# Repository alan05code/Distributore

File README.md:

# Distributore
Distributore Smart | Progetto Scolastico 2023/2024 | Client (PCB) + Server(RaspBerry) + SitoWeb(HTML/CSS/JavaScript) + Simulazione(Python)

Progetto esposto agli Open Day. Documentazione non terminata.

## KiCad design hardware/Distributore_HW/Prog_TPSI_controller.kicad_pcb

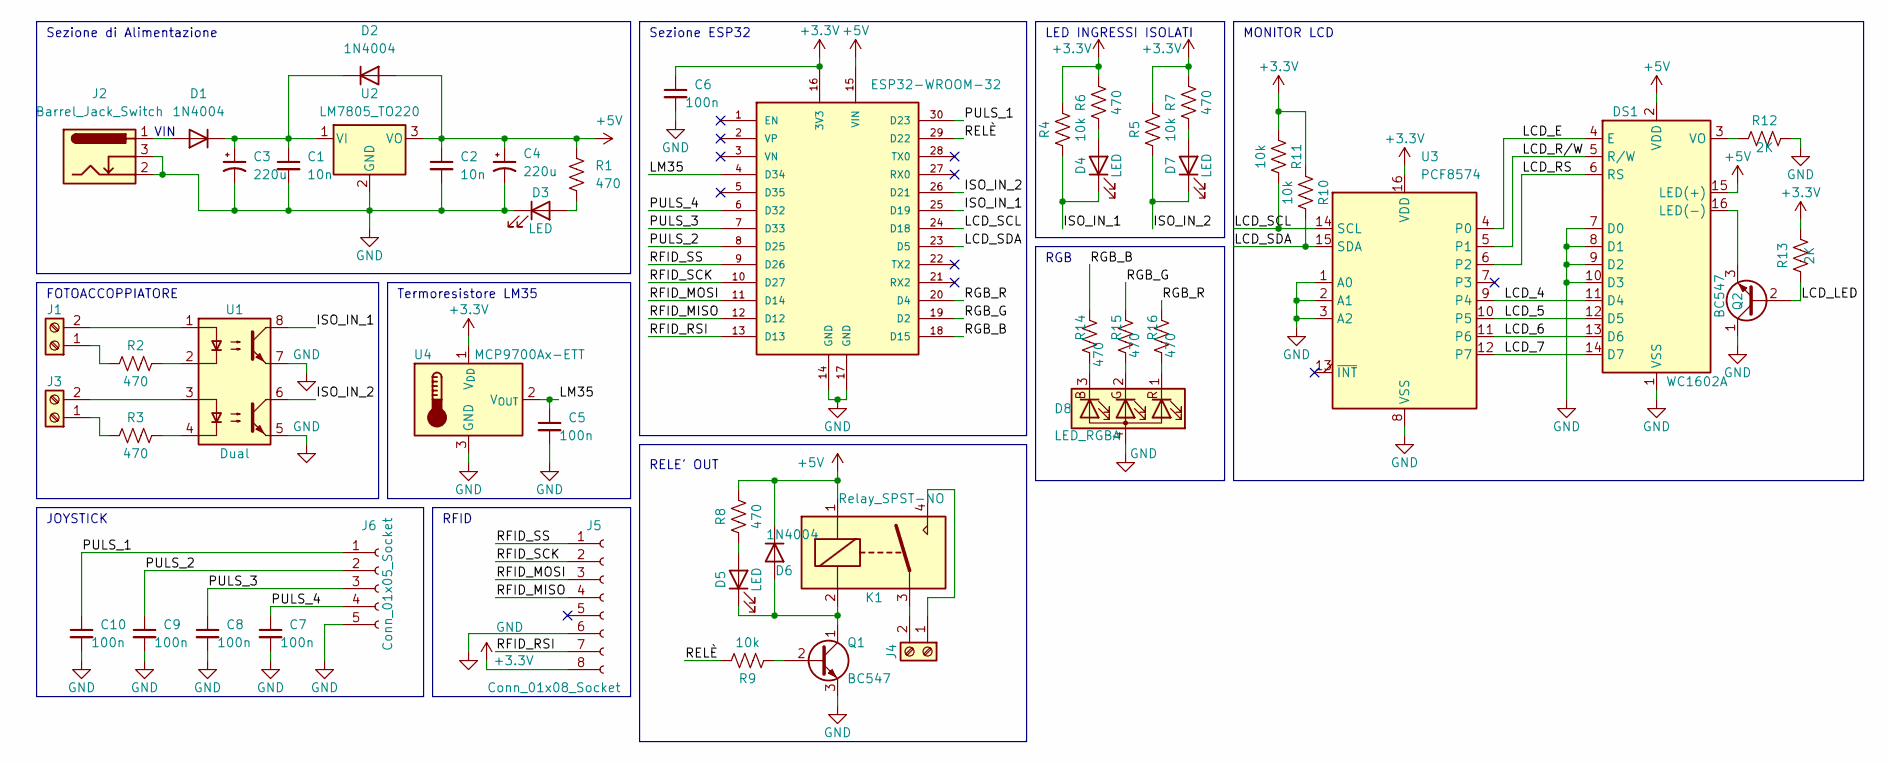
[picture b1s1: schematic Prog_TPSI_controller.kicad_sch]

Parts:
C1, C2: 10n; C_Disc_D7.0mm_W2.5mm_P5.00mm
C3, C4: 220u; CP_Radial_D5.0mm_P2.50mm
C5, C6, C7, C8, C9, C10: 100n; C_Disc_D7.0mm_W2.5mm_P5.00mm
D1, D2: 1N4004; D_DO-41_SOD81_P10.16mm_Horizontal
D3, D4, D5, D7: LED; LED_D5.0mm
D6: 1N4004; D_DO-41_SOD81_P7.62mm_Horizontal
D8: LED_RGBA; LED_D5.0mm-4_RGB_Wide_Pins
DS1: WC1602A; LCD
J1, J3, J4: Screw_Terminal_01x02; TerminalBlock_bornier-2_P5.08mm
J2: Barrel_Jack_Switch; Connettore_Alimentazione_Femmina_2.5mm
J5: Conn_01x08_Socket; PinSocket_1x08_P2.54mm_Horizontal
J6: Conn_01x05_Socket; PinSocket_1x05_P2.54mm_Horizontal
K1: Relay_SPST-NO; Rele_HF33F_CodiceRS_176-2640
Q1, Q2: BC547; TO-92L_Inline_Wide
R1, R8: 470; R_Axial_DIN0207_L6.3mm_D2.5mm_P7.62mm_Horizontal
R2, R3, R6, R7, R14, R15, R16: 470; R_Axial_DIN0207_L6.3mm_D2.5mm_P10.16mm_Horizontal
R4, R5, R10, R11: 10k; R_Axial_DIN0207_L6.3mm_D2.5mm_P10.16mm_Horizontal
R9: 10k; R_Axial_DIN0207_L6.3mm_D2.5mm_P15.24mm_Horizontal
R12: 2K; R_Axial_DIN0207_L6.3mm_D2.5mm_P10.16mm_Horizontal
R13: 2K; R_Axial_DIN0207_L6.3mm_D2.5mm_P7.62mm_Horizontal
S1: ESP32-WROOM-32; MODULE_ESP32_DEVKIT_V1; PARTREV N/A
U1: Dual; Socket_DIP-8_dual_DIP-4
U2: LM7805_TO220; TO-220-3_Horizontal_TabUp
U3: PCF8574; DIP-16_W7.62mm_Socket
U4: MCP9700Ax-ETT; TO-92_Inline_Wide

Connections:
+3.3V: C6.1, J5.8, R4.2, R5.2, R6.2, R7.2, R10.1, R11.1, R13.2, S1.16 (3V3), U3.16 (VDD), U4.1 (V_{DD})
+5V: C2.1, C4.1, D2.2 (A), D6.1 (K), DS1.2 (VDD), DS1.15 (LED(+)), K1.1, R1.1, R8.2, S1.15 (VIN), U2.3 (VO)
/ISO_IN_1: D4.1 (K), R4.1, S1.25 (D19), U1.8
/ISO_IN_2: D7.1 (K), R5.1, S1.26 (D21), U1.6
/LCD_4: DS1.11 (D4), U3.9 (P4)
/LCD_5: DS1.12 (D5), U3.10 (P5)
/LCD_6: DS1.13 (D6), U3.11 (P6)
/LCD_7: DS1.14 (D7), U3.12 (P7)
/LCD_E: DS1.4 (E), U3.4 (P0)
/LCD_LED: Q2.2 (B), R13.1
/LCD_RS: DS1.6 (RS), U3.6 (P2)
/LCD_R/W: DS1.5 (R/W), U3.5 (P1)
/LCD_SCL: R11.2, S1.24 (D18), U3.14 (SCL)
/LCD_SDA: R10.2, S1.23 (D5), U3.15 (SDA)
/LM35: C5.1, S1.4 (D34), U4.2 (V_{OUT})
/PULS_1: C10.1, J6.1, S1.30 (D23)
/PULS_2: C9.1, J6.2, S1.8 (D25)
/PULS_3: C8.1, J6.3, S1.7 (D33)
/PULS_4: C7.1, J6.4, S1.6 (D32)
/RELÈ: R9.2, S1.29 (D22)
/RFID_MISO: J5.4, S1.12 (D12)
/RFID_MOSI: J5.3, S1.11 (D14)
/RFID_RSI: J5.7, S1.13 (D13)
/RFID_SCK: J5.2, S1.10 (D27)
/RFID_SS: J5.1, S1.9 (D26)
/RGB_B: R14.2, S1.18 (D15)
/RGB_G: R15.2, S1.19 (D2)
/RGB_R: R16.2, S1.20 (D4)
GND: C1.2, C2.2, C3.2, C4.2, C5.2, C6.2, C7.2, C8.2, C9.2, C10.2, D3.1 (K), D8.4 (A), DS1.1 (VSS), DS1.7 (D0), DS1.8 (D1), DS1.9 (D2), DS1.10 (D3), J2.2, J2.3, J5.6, J6.5, Q1.3 (E), Q2.1 (C), R12.2, S1.14 (GND), S1.17 (GND), U1.5, U1.7, U2.2 (GND), U3.1 (A0), U3.2 (A1), U3.3 (A2), U3.8 (VSS), U4.3 (GND)
unnamed: D1.2 (A), J2.1
unnamed: C1.1, C3.1, D1.1 (K), D2.1 (K), U2.1 (VI)
unnamed: D3.2 (A), R1.2
unnamed: D4.2 (A), R6.1
unnamed: D5.2 (A), R8.1
unnamed: D5.1 (K), D6.2 (A), K1.2, Q1.1 (C)
unnamed: D7.2 (A), R7.1
unnamed: D8.3 (BK), R14.1
unnamed: D8.2 (GK), R15.1
unnamed: D8.1 (RK), R16.1
unnamed: DS1.16 (LED(-)), Q2.3 (E)
unnamed: DS1.3 (VO), R12.1
unnamed: J1.1, R2.1
unnamed: J1.2, U1.1
unnamed: J3.1, R3.1
unnamed: J3.2, U1.3
unnamed: J4.1, K1.4
unnamed: J4.2, K1.3
unnamed: Q1.2 (B), R9.1
unnamed: R2.2, U1.2
unnamed: R3.2, U1.4

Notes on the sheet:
RFID
MONITOR LCD
Sezione ESP32
RGB
Sezione di Alimentazione
JOYSTICK
Termoresistore LM35
RELE' OUT
VIN
LED INGRESSI ISOLATI
FOTOACCOPPIATORE

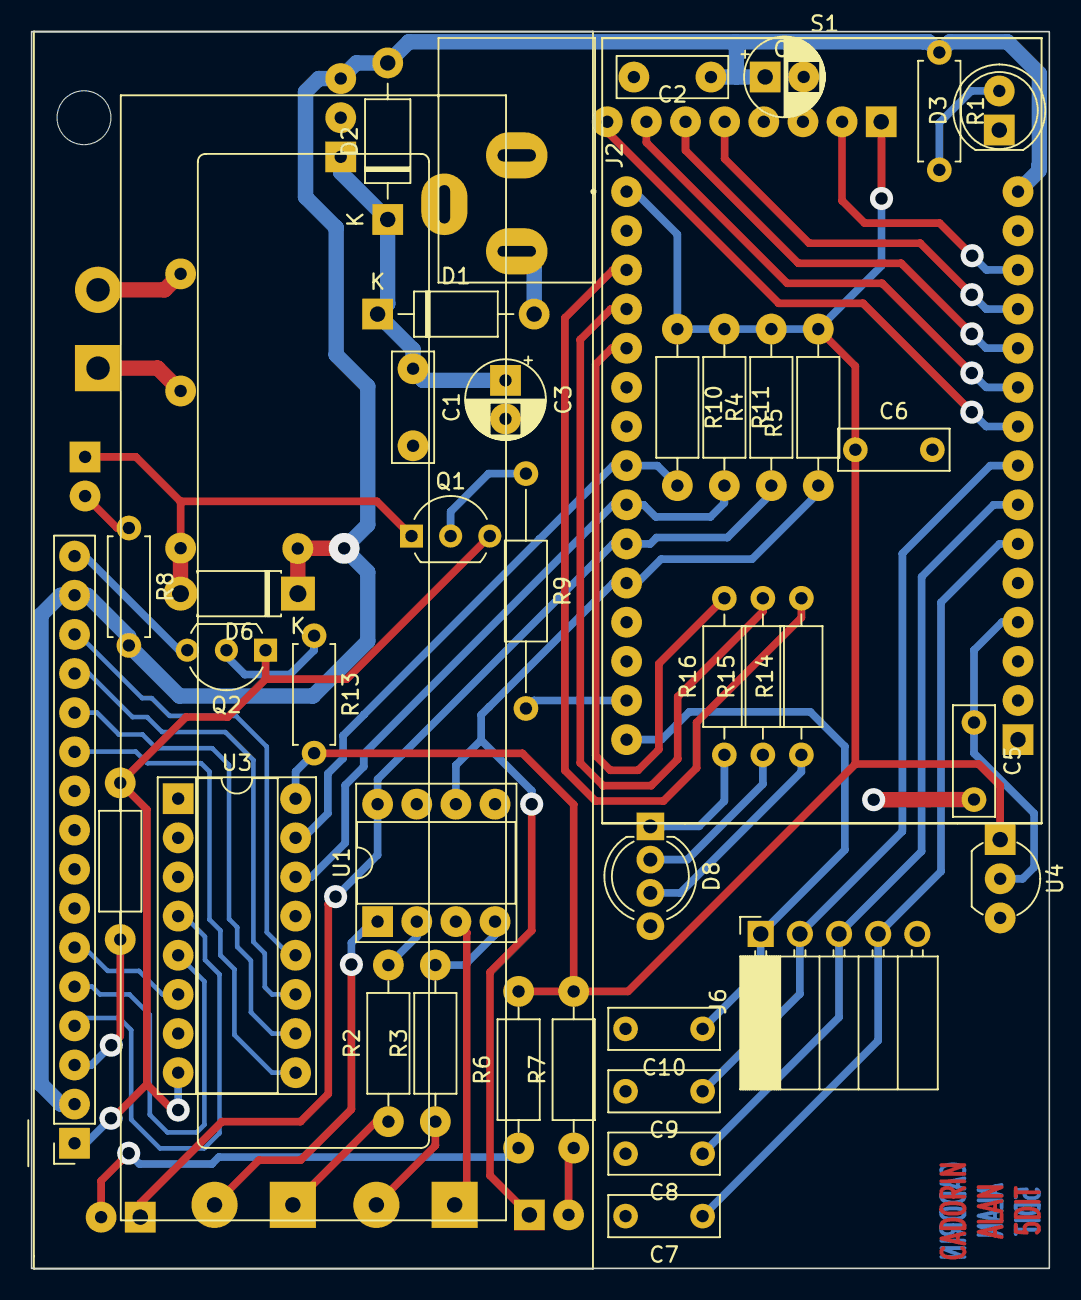
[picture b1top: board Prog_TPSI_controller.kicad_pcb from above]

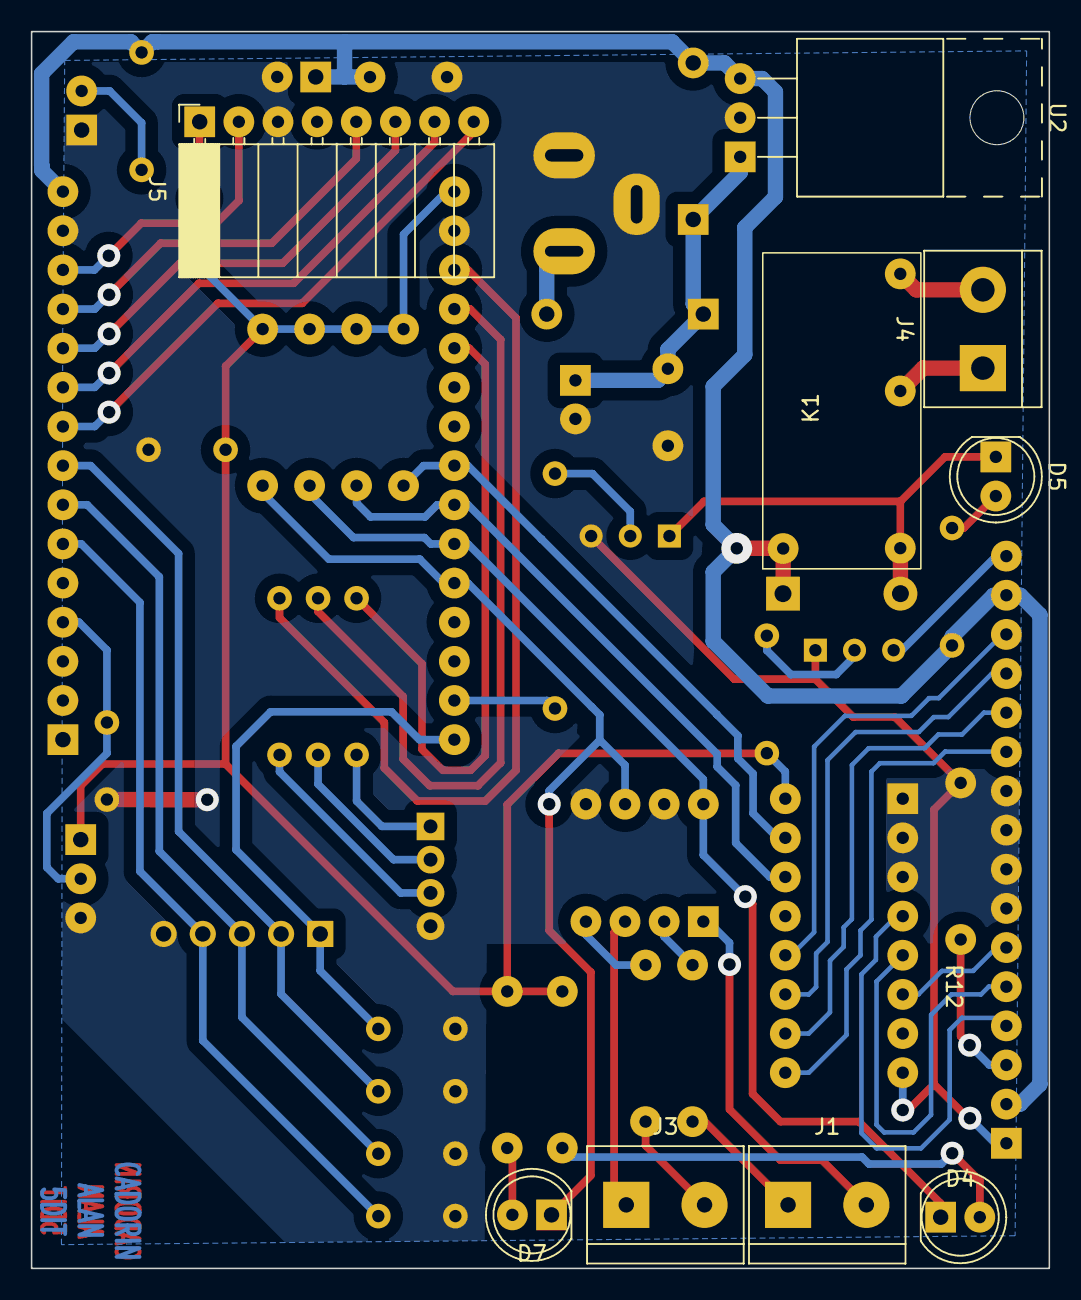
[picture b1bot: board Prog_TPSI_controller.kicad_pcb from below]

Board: 2 copper layers, 66.0 x 80.3 mm, 49 parts (9 on the bottom side), 50 nets.

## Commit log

2025-02-07 Distributore Smart v2.0
